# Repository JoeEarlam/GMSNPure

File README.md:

# GMSNPure
An attempt to collate all GMSN's open source designs since the site went offline.

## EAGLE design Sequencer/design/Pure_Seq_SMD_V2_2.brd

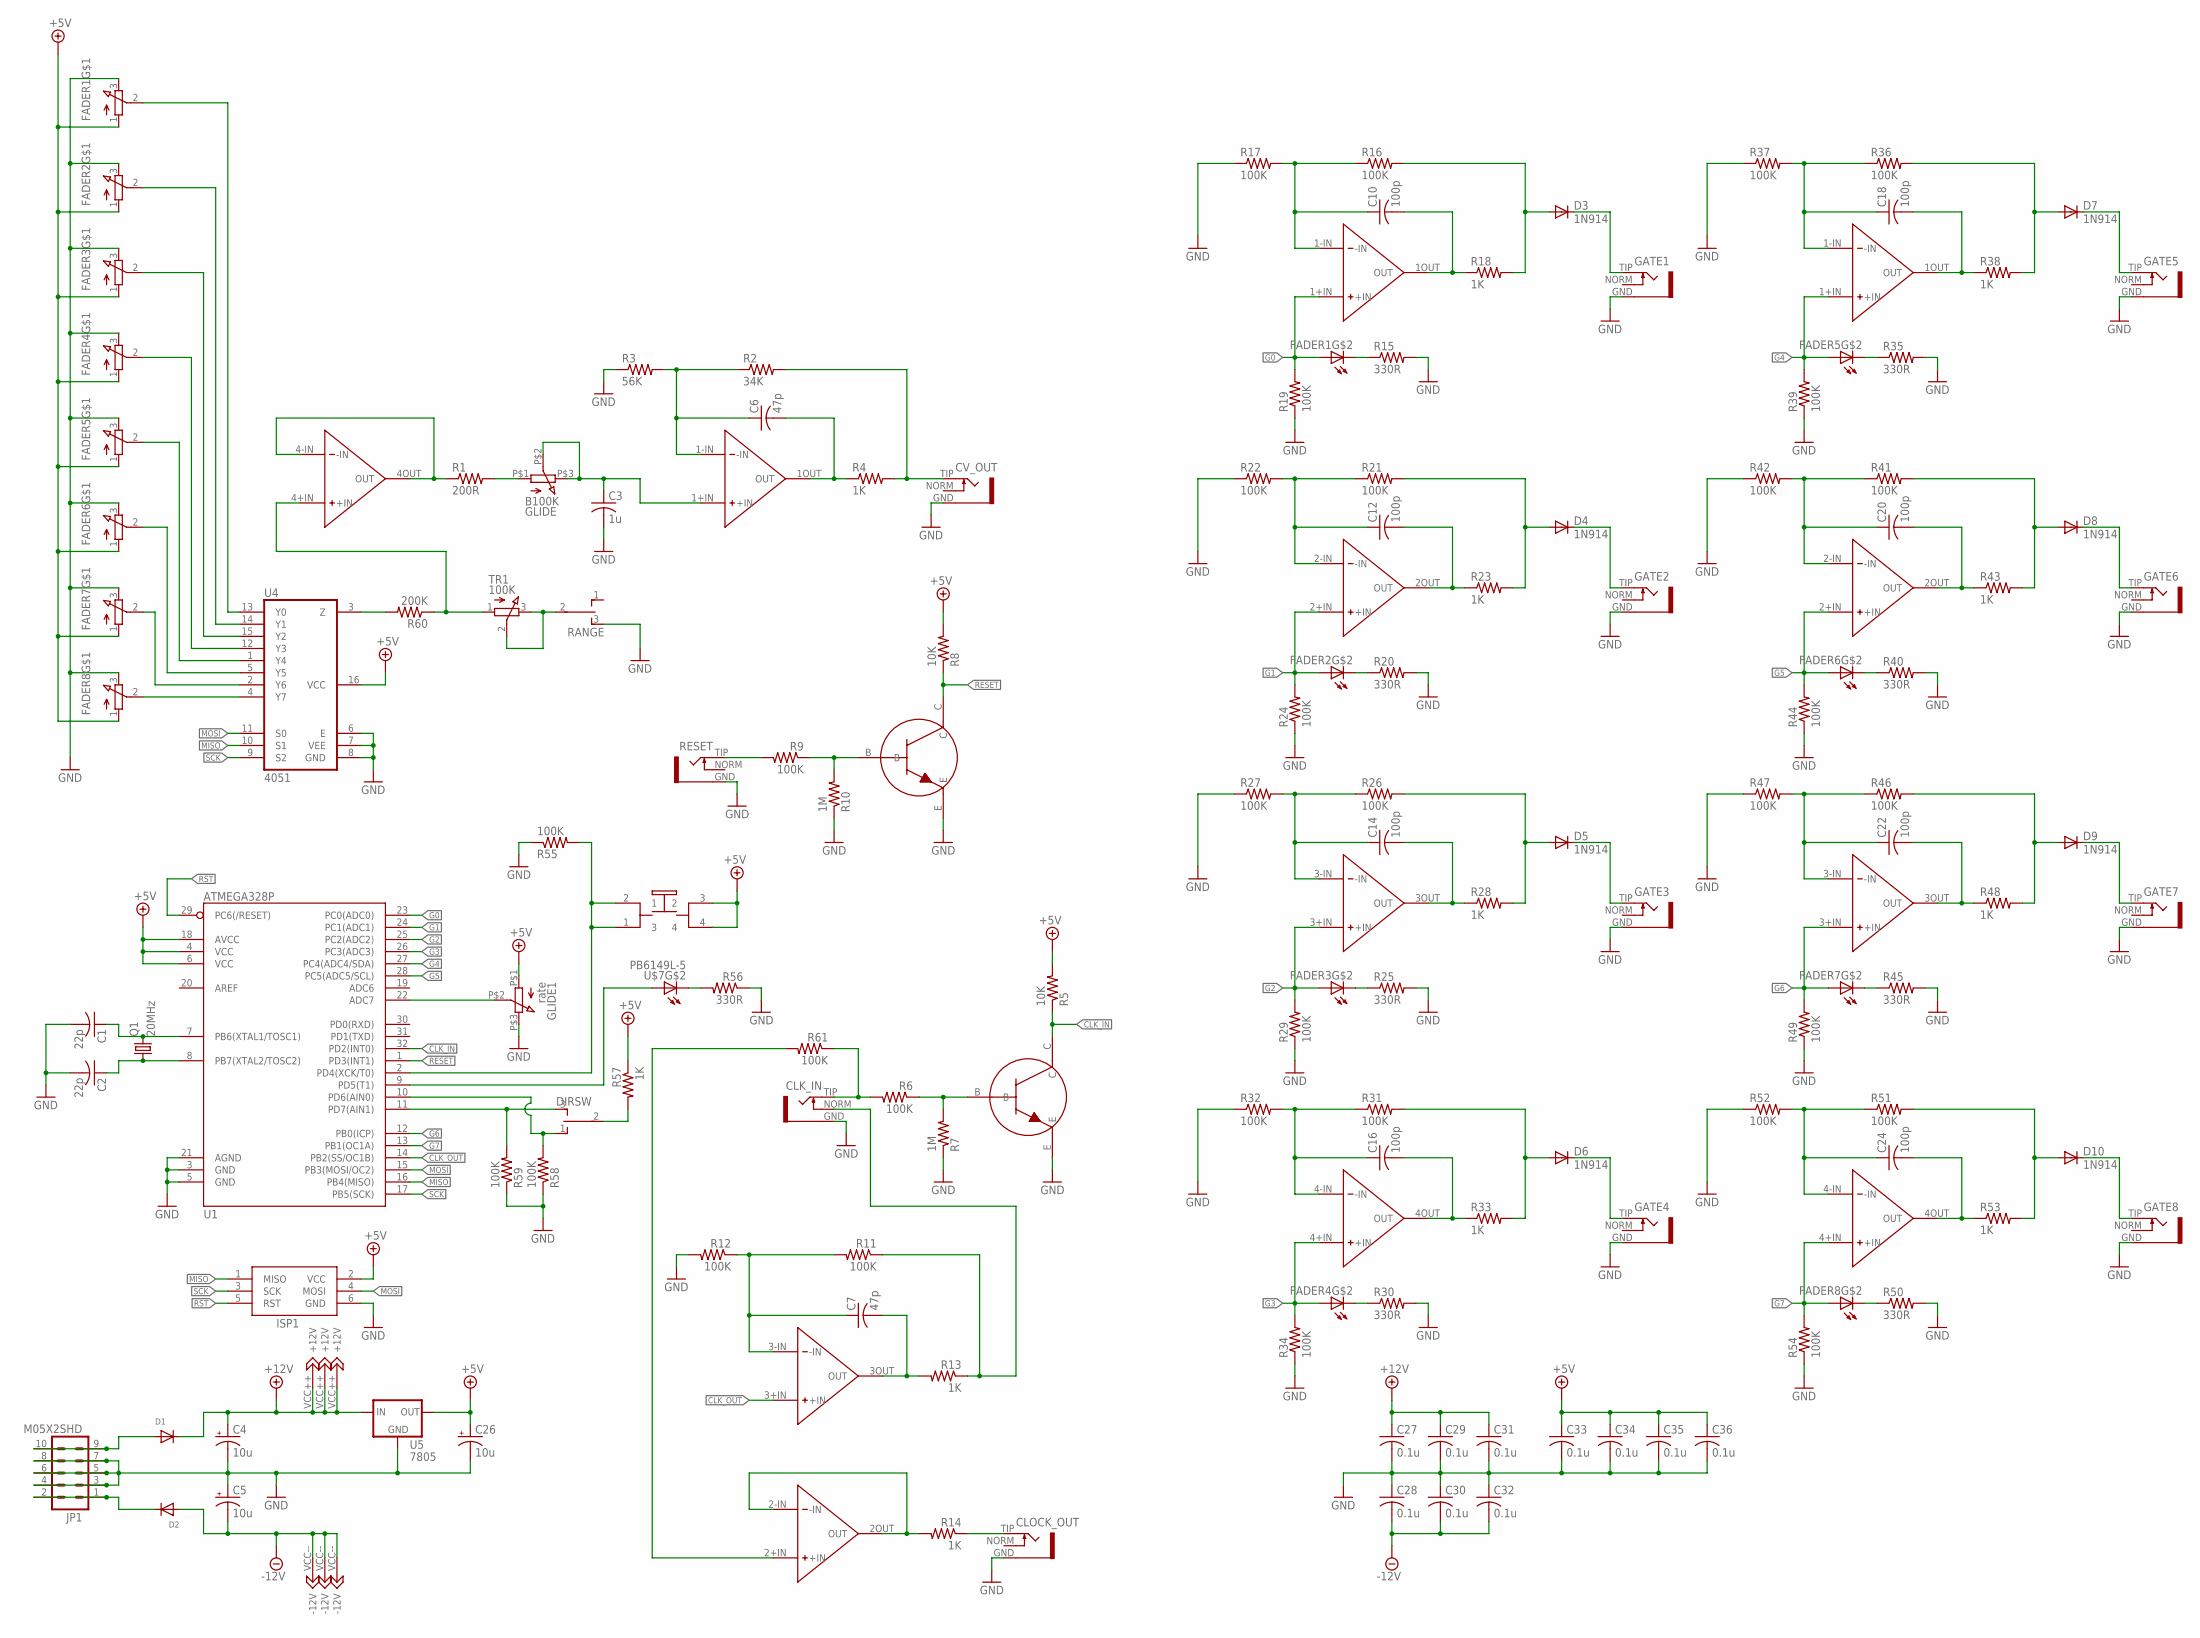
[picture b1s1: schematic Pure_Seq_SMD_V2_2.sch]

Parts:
C1, C2: 22p; C0805K
C3: 1u; C0805K
C4, C5, C26: 10u; 153CLV-0505
C6, C7: 47p; C0805K
C10, C12, C14, C16, C18, C20, C22, C24: 100p; C0805K
C27, C28, C29, C30, C31, C32, C33, C34, C35, C36: 0.1u; C0805K
CLK_IN: S_JACK
CLOCK_OUT: S_JACK
CV_OUT: S_JACK
D1, D2: DIODESMA; SMADIODE
D3, D4, D5, D6, D7, D8, D9, D10: 1N914; SOD-323
DIRSW: TOGGLE_ON_OFF_ON
FADER1, FADER2, FADER3, FADER4, FADER5, FADER6, FADER7, FADER8: LED_FADER
GATE1, GATE2, GATE3, GATE4, GATE5, GATE6, GATE7, GATE8: S_JACK
GLIDE: B100K; Q-POT
GLIDE1: rate; Q-POT
ISP1: AVRISP-6; AVRISP
JP1: M05X2SHD; 2X5-SHROUDED
Q1: 20MHz; HC49UP
R1: 200R; R0805
R2: 34K; R0805
R3: 56K; R0805
R4, R13, R14, R18, R23, R28, R33, R38, R43, R48, R53, R57: 1K; R0805
R5, R8: 10K; R0805
R6, R9, R11, R12, R16, R17, R19, R21, R22, R24, R26, R27, R29, R31, R32, R34, R36, R37, R39, R41, R42, R44, R46, R47, R49, R51, R52, R54, R55, R58, R59, R61: 100K; R0805
R7, R10: 1M; R0805
R15, R20, R25, R30, R35, R40, R45, R50, R56: 330R; R0805
R60: 200K; R0805
RANGE: TOGGLE_ON_OFF_ON
RESET: S_JACK
T1, T2: 2N3904; TRANSISTOR_SINGLE_N-TYPE
TR1: 100K; TRIMMER_TH3
U1: ATMEGA328P; TQFP32-08
U2, U3, U6: QUAD_OPAMP
U4: 4051; N2222_ARRAY
U5: 7805; V-REG
U$7: PB6149L-5; PB6149L

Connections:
+5V: C26.+, C33.1, C34.1, C35.1, C36.1, FADER1.1, FADER2.1, FADER3.1, FADER4.1, FADER5.1, FADER6.1, FADER7.1, FADER8.1, GLIDE1.P$1 (1), ISP1.2 (VCC), R5.2, R8.2, R57.1, U1.4 (VCC), U1.6 (VCC), U1.18 (AVCC), U4.16 (VCC), U5.3 (OUT), U$7.3 (2), U$7.4
+12V: C4.+, C27.1, C29.1, C31.1, D1.C, U2.VCC++ (+12V), U3.VCC++ (+12V), U5.1 (IN), U6.VCC++ (+12V)
-12V: C5.-, C28.2, C30.2, C32.2, D2.A, U2.VCC-- (-12V), U3.VCC-- (-12V), U6.VCC-- (-12V)
CLK_IN: R5.1, T1.C, U1.32 (PD2(INT0))
CLK_OUT: U1.14 (PB2(SS/OC1B)), U6.3+IN (+IN)
G0: FADER1.A, R19.2, U1.23 (PC0(ADC0)), U2.1+IN (+IN)
G1: FADER2.A, R24.2, U1.24 (PC1(ADC1)), U2.2+IN (+IN)
G2: FADER3.A, R29.2, U1.25 (PC2(ADC2)), U2.3+IN (+IN)
G3: FADER4.A, R34.2, U1.26 (PC3(ADC3)), U2.4+IN (+IN)
G4: FADER5.A, R39.2, U1.27 (PC4(ADC4/SDA)), U3.1+IN (+IN)
G5: FADER6.A, R44.2, U1.28 (PC5(ADC5/SCL)), U3.2+IN (+IN)
G6: FADER7.A, R49.2, U1.12 (PB0(ICP)), U3.3+IN (+IN)
G7: FADER8.A, R54.2, U1.13 (PB1(OC1A)), U3.4+IN (+IN)
GND: C1.2, C2.2, C3.2, C4.-, C5.+, C26.-, C27.2, C28.1, C29.2, C30.1, C31.2, C32.1, C33.2, C34.2, C35.2, C36.2, CLK_IN.GND, CLOCK_OUT.GND, CV_OUT.GND, FADER1.3, FADER2.3, FADER3.3, FADER4.3, FADER5.3, FADER6.3, FADER7.3, FADER8.3, GATE1.GND, GATE2.GND, GATE3.GND, GATE4.GND, GATE5.GND, GATE6.GND, GATE7.GND, GATE8.GND, GLIDE1.P$3 (3), ISP1.6 (GND), JP1.3, JP1.4, JP1.5, JP1.6, JP1.7, JP1.8, R3.1, R7.1, R10.1, R12.2, R15.2, R17.1, R19.1, R20.2, R22.1, R24.1, R25.2, R27.1, R29.1, R30.2, R32.1, R34.1, R35.2, R37.1, R39.1, R40.2, R42.1, R44.1, R45.2, R47.1, R49.1, R50.2, R52.1, R54.1, R55.1, R56.1, R58.1, R59.1, RANGE.3 (S), RESET.GND, T1.E, T2.E, U1.3 (GND), U1.5 (GND), U1.21 (AGND), U4.6 (E), U4.7 (VEE), U4.8 (GND), U5.4 (GND)
MISO: ISP1.1 (MISO), U1.16 (PB4(MISO)), U4.10 (S1)
MOSI: ISP1.4 (MOSI), U1.15 (PB3(MOSI/OC2)), U4.11 (S0)
unnamed: C1.1, Q1.2, U1.7 (PB6(XTAL1/TOSC1))
unnamed: C2.1, Q1.1, U1.8 (PB7(XTAL2/TOSC2))
unnamed: R60.1, TR1.1, U6.4+IN (+IN)
unnamed: R1.1, U6.4-IN (-IN), U6.4OUT (OUT)
unnamed: GLIDE.P$1 (1), R1.2
unnamed: FADER8.2, U4.4 (Y7)
unnamed: FADER7.2, U4.2 (Y6)
unnamed: FADER6.2, U4.5 (Y5)
unnamed: D1.A, JP1.9, JP1.10
unnamed: D2.C, JP1.1, JP1.2
unnamed: FADER5.2, U4.1 (Y4)
unnamed: FADER4.2, U4.12 (Y3)
unnamed: FADER3.2, U4.15 (Y2)
unnamed: FADER2.2, U4.14 (Y1)
unnamed: FADER1.2, U4.13 (Y0)
unnamed: C3.1, GLIDE.P$2 (2), GLIDE.P$3 (3), U6.1+IN (+IN)
unnamed: R6.1, R7.2, T1.B
unnamed: R61.2, U6.2+IN (+IN)
unnamed: C6.1, R2.1, R3.2, U6.1-IN (-IN)
unnamed: C6.2, R4.1, U6.1OUT (OUT)
unnamed: CV_OUT.TIP, R2.2, R4.2
unnamed: R9.1, R10.2, T2.B
unnamed: R9.2, RESET.TIP
unnamed: C7.1, R11.2, R12.1, U6.3-IN (-IN)
unnamed: C7.2, R13.2, U6.3OUT (OUT)
unnamed: CLK_IN.TIP, R6.2, R61.1
unnamed: R14.2, U6.2-IN (-IN), U6.2OUT (OUT)
unnamed: CLOCK_OUT.TIP, R14.1
unnamed: CLK_IN.NORM, R11.1, R13.1
unnamed: GLIDE1.P$2 (2), U1.22 (ADC7)
unnamed: FADER1.K (C), R15.1
unnamed: C10.1, R16.1, R17.2, U2.1-IN (-IN)
unnamed: C10.2, R18.1, U2.1OUT (OUT)
unnamed: D3.2 (A), R16.2, R18.2
unnamed: FADER3.K (C), R25.1
unnamed: FADER2.K (C), R20.1
unnamed: C12.1, R21.1, R22.2, U2.2-IN (-IN)
unnamed: C12.2, R23.1, U2.2OUT (OUT)
unnamed: D4.2 (A), R21.2, R23.2
unnamed: C14.1, R26.1, R27.2, U2.3-IN (-IN)
unnamed: C14.2, R28.1, U2.3OUT (OUT)
unnamed: D5.2 (A), R26.2, R28.2
unnamed: FADER4.K (C), R30.1
unnamed: C16.1, R31.1, R32.2, U2.4-IN (-IN)
unnamed: C16.2, R33.1, U2.4OUT (OUT)
unnamed: D6.2 (A), R31.2, R33.2
unnamed: FADER5.K (C), R35.1
unnamed: C18.1, R36.1, R37.2, U3.1-IN (-IN)
unnamed: C18.2, R38.1, U3.1OUT (OUT)
unnamed: D7.2 (A), R36.2, R38.2
unnamed: FADER6.K (C), R40.1
unnamed: C20.1, R41.1, R42.2, U3.2-IN (-IN)
unnamed: C20.2, R43.1, U3.2OUT (OUT)
unnamed: D8.2 (A), R41.2, R43.2
unnamed: FADER7.K (C), R45.1
unnamed: C22.1, R46.1, R47.2, U3.3-IN (-IN)
unnamed: C22.2, R48.1, U3.3OUT (OUT)
unnamed: D9.2 (A), R46.2, R48.2
unnamed: FADER8.K (C), R50.1
unnamed: C24.1, R51.1, R52.2, U3.4-IN (-IN)
unnamed: C24.2, R53.1, U3.4OUT (OUT)
unnamed: D10.2 (A), R51.2, R53.2
unnamed: R55.2, U1.2 (PD4(XCK/T0)), U$7.1 (3), U$7.2 (1)
unnamed: U1.9 (PD5(T1)), U$7.A
unnamed: R56.2, U$7.K (C)
unnamed: DIRSW.2, R57.2
unnamed: DIRSW.1 (O), R58.2, U1.10 (PD6(AIN0))
unnamed: DIRSW.3 (S), R59.2, U1.11 (PD7(AIN1))
unnamed: R60.2, U4.3 (Z)
unnamed: RANGE.2, TR1.2, TR1.3
unnamed: D6.1 (C), GATE4.TIP
unnamed: D5.1 (C), GATE3.TIP
unnamed: D4.1 (C), GATE2.TIP
unnamed: D3.1 (C), GATE1.TIP
unnamed: D10.1 (C), GATE8.TIP
unnamed: D9.1 (C), GATE7.TIP
unnamed: D8.1 (C), GATE6.TIP
unnamed: D7.1 (C), GATE5.TIP
RESET: R8.1, T2.C, U1.1 (PD3(INT1))
RST: ISP1.5 (RST), U1.29 (PC6(/RESET))
SCK: ISP1.3 (SCK), U1.17 (PB5(SCK)), U4.9 (S2)

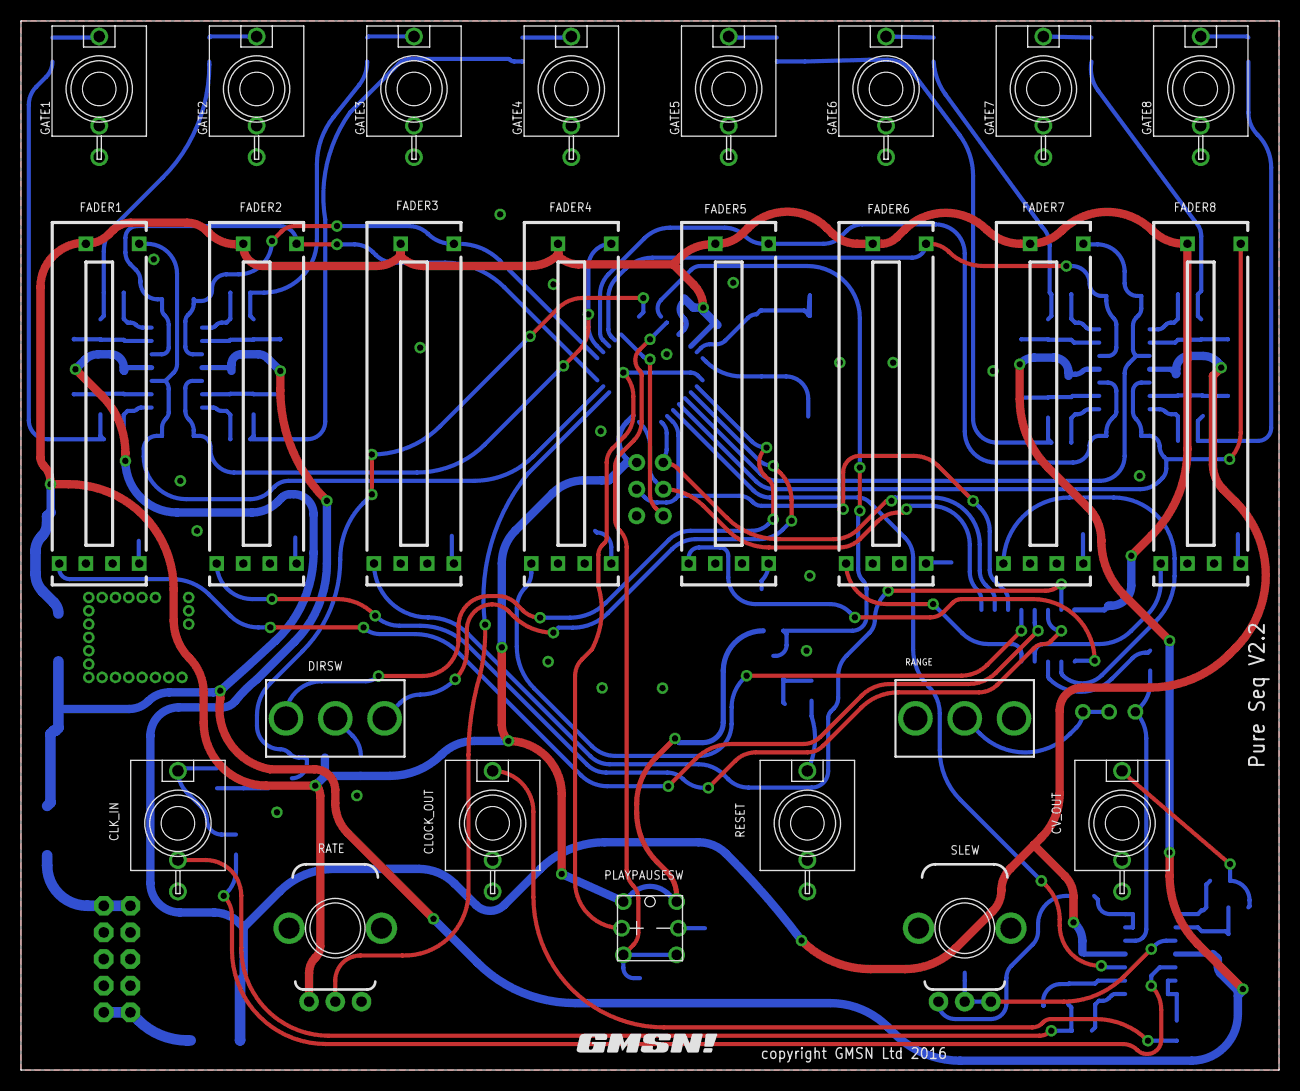
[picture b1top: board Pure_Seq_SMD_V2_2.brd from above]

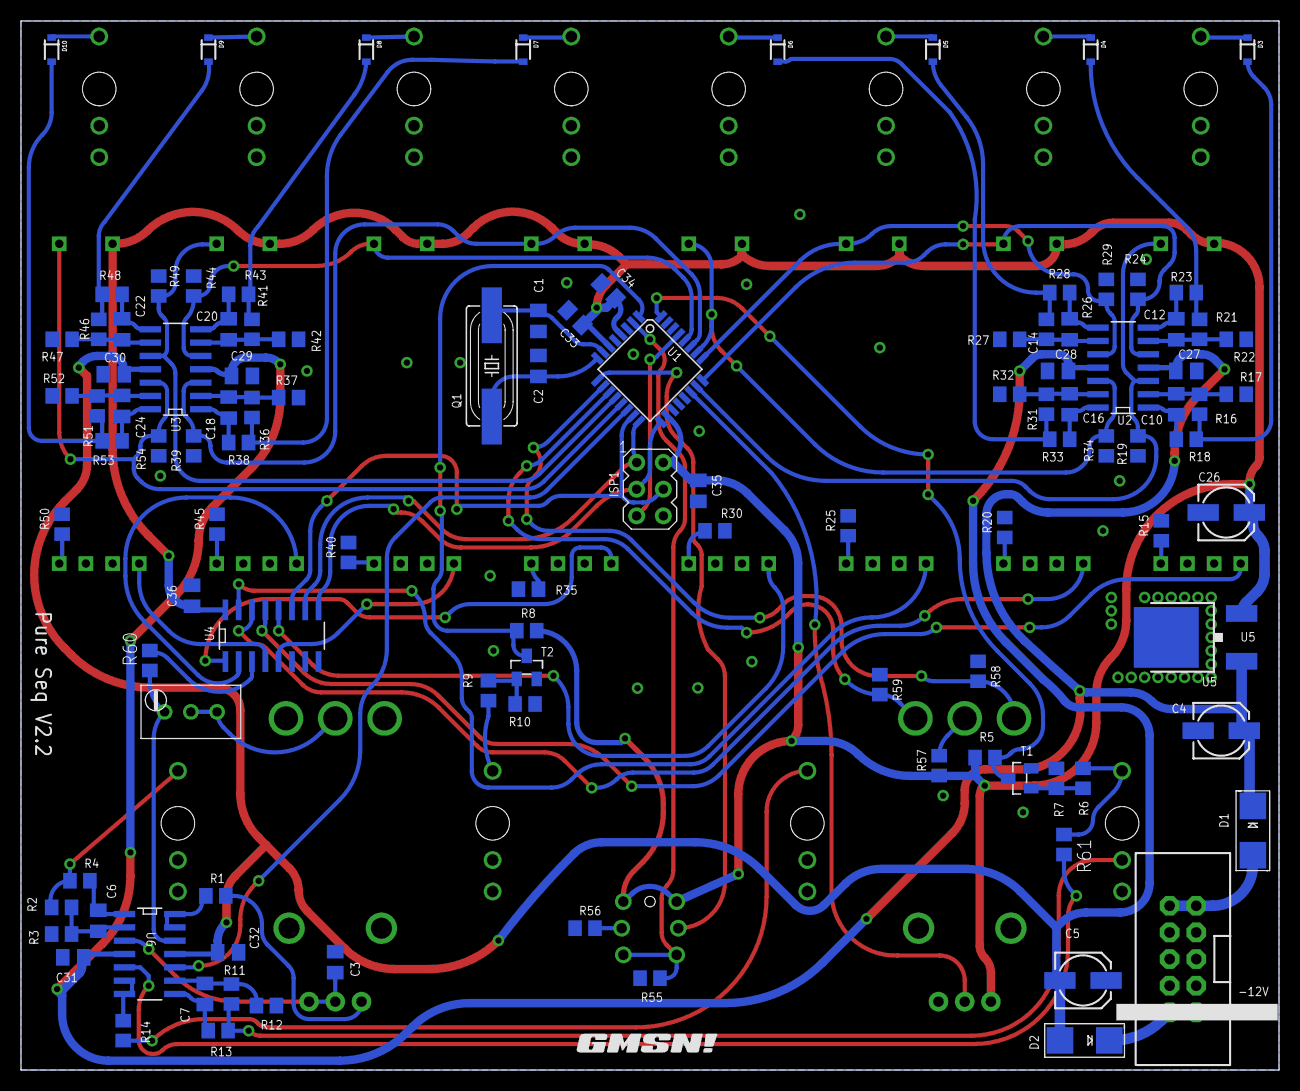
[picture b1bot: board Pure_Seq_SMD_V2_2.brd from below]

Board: 2 copper layers, 119.9 x 100.0 mm, 136 parts (110 on the bottom side), 97 nets.

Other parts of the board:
U$1, U$2: GMSN!_LOGO

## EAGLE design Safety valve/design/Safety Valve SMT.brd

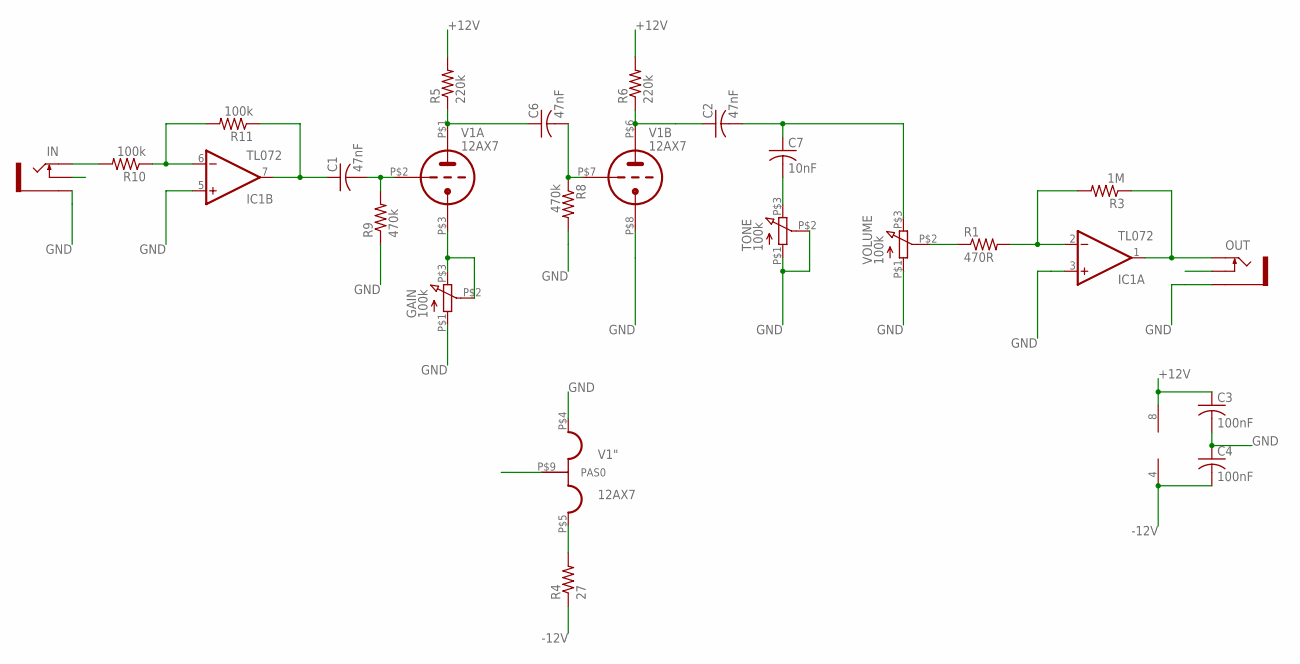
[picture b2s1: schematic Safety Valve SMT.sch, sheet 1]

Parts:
C1, C2, C6: 47nF; C025-024X044
C3, C4: 100nF; C025-024X044
C7: 10nF; C050-024X044
GAIN: 100k; POTENTIOMETER_9MM
IC1: TL072; DIL08
IN: SOCKET_MONO_3.5MMPJ301M-12; PJ301M-12
OUT: SOCKET_MONO_3.5MMPJ301M-12; PJ301M-12
R1: 470R; M0805
R3: 1M; M0805
R4: 27; R0805
R5: 220k; M0805
R6: 220k; R0805
R8, R9: 470k; M0805
R10: 100k; R0805
R11: 100k; M0805
TONE: 100k; POTENTIOMETER_9MM
V1: 12AX7
VOLUME: 100k; POTENTIOMETER_9MM

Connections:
+12V: C3.1, IC1.8 (V+), R5.2, R6.2; also elsewhere on the board
-12V: C4.2, IC1.4 (V-), R4.1; also elsewhere on the board
GND: C3.2, C4.1, GAIN.P$1 (1), IC1.3 (+IN), IC1.5 (+IN), IN.GND (SLEEVE), OUT.GND (SLEEVE), R8.2, R9.1, TONE.P$1 (1), TONE.P$2 (2), V1.P$4 (H1), V1.P$8 (TK), VOLUME.P$1 (1); also elsewhere on the board
unnamed: GAIN.P$2 (2), GAIN.P$3 (3), V1.P$3 (TK)
unnamed: IC1.2 (-IN), R1.2, R3.2
unnamed: C2.2, C7.1, VOLUME.P$3 (3)
unnamed: IC1.1 (OUT), OUT.TIP, R3.1
unnamed: C2.1, R6.1, V1.P$6 (TA)
unnamed: C6.1, R5.1, V1.P$1 (TA)
unnamed: C1.2, R9.2, V1.P$2 (TG)
unnamed: C1.1, IC1.7 (OUT), R11.1
unnamed: R4.2, V1.P$5 (H3)
unnamed: C6.2, R8.1, V1.P$7 (TG)
unnamed: IN.TIP, R10.2
unnamed: C7.2, TONE.P$3 (3)
unnamed: IC1.6 (-IN), R10.1, R11.2
unnamed: R1.1, VOLUME.P$2 (2)

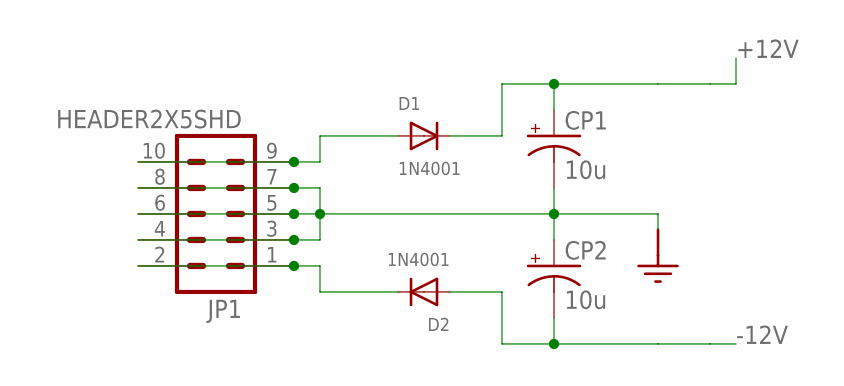
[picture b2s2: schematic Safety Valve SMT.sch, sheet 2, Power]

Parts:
CP1, CP2: 10u; SANYO-OSCON_D
D1, D2: 1N4001; DO-1N4148
JP1: HEADER2X5SHD; 2X5-SHROUDED

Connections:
+12V: CP1.+, D1.C; also elsewhere on the board
-12V: CP2.-, D2.A; also elsewhere on the board
GND: CP1.-, CP2.+, JP1.3, JP1.4, JP1.5, JP1.6, JP1.7, JP1.8; also elsewhere on the board
unnamed: D1.A, JP1.9, JP1.10
unnamed: D2.C, JP1.1, JP1.2

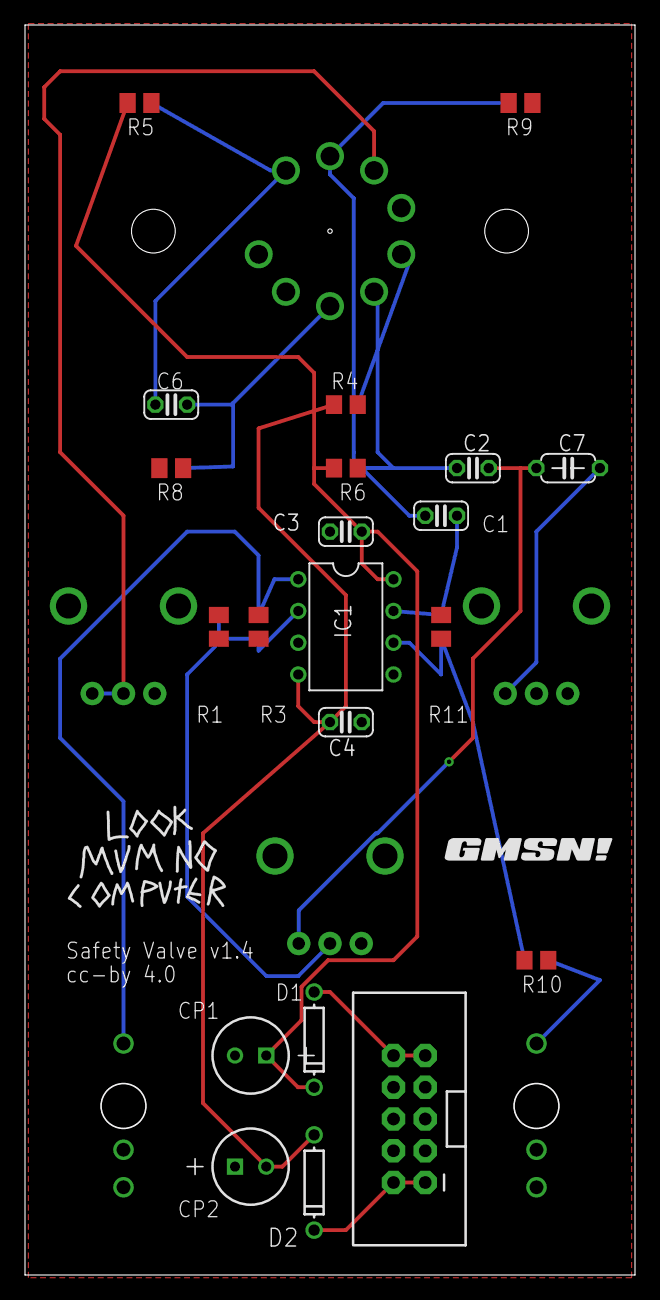
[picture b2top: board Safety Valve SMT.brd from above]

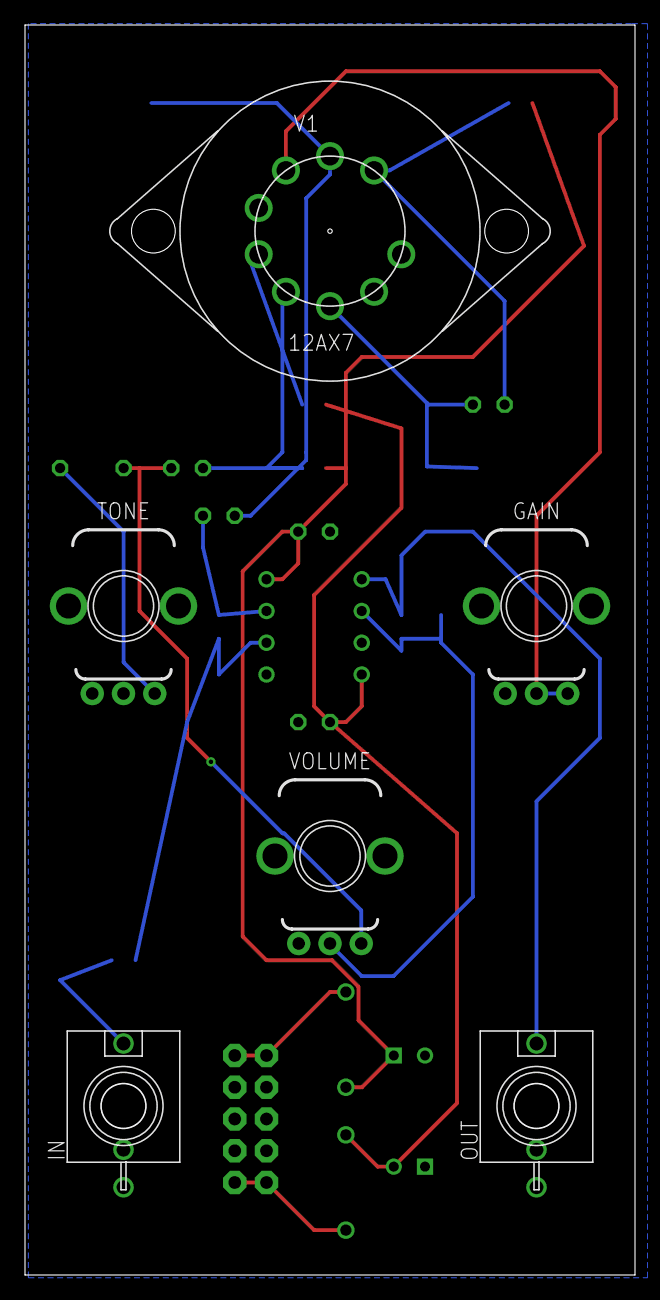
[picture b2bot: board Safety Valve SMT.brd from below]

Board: 2 copper layers, 48.8 x 100.0 mm, 29 parts (6 on the bottom side), 19 nets.

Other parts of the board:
U$1: LMNC_LOGO
U$2: GMSN!_LOGO

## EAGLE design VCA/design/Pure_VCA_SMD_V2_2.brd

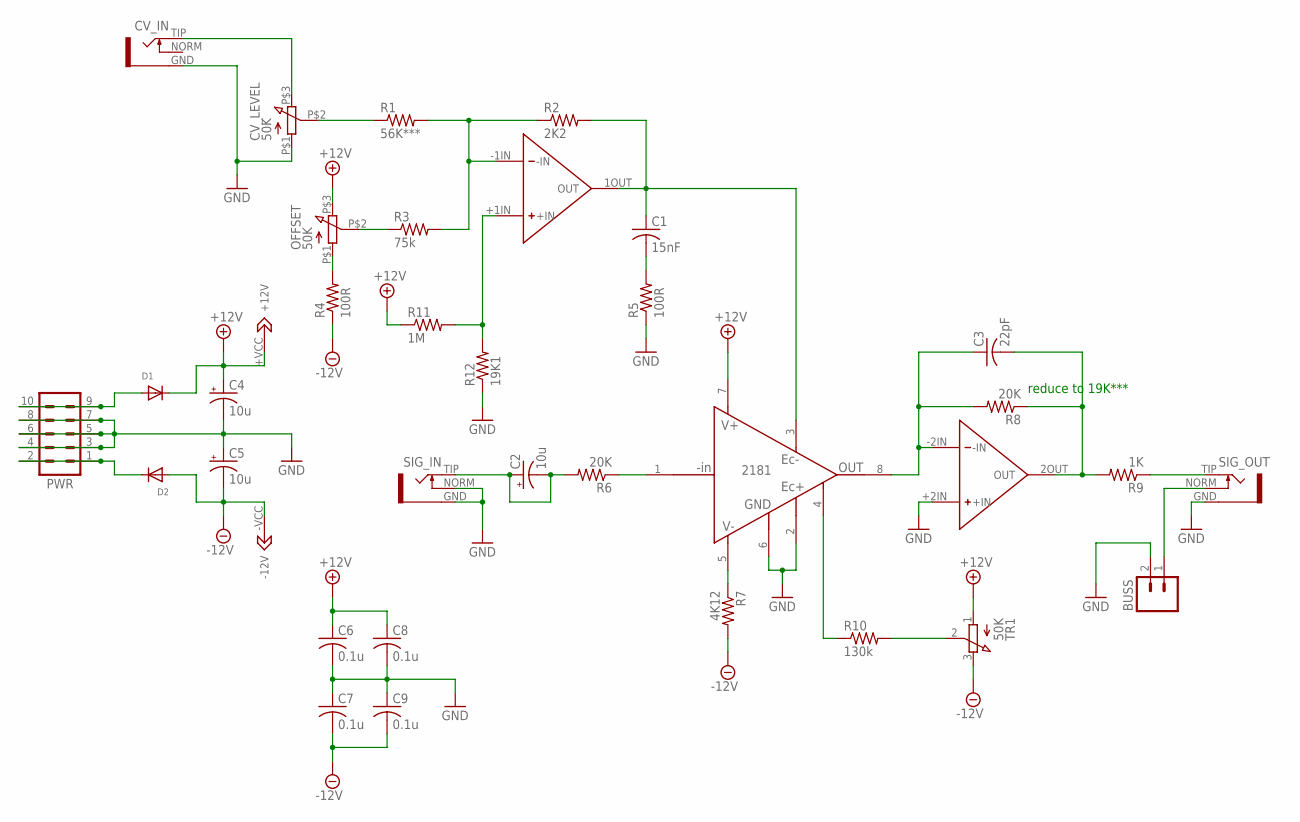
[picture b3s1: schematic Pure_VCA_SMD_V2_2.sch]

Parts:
BUSS: M02PTH; 1X02
C1: 15nF; C0805K
C2, C4, C5: 10u; 153CLV-0505
C3: 22pF; C0805K
C6, C7, C8, C9: 0.1u; C0805K
CV_IN: S_JACK
CV_LEVEL: 50K; Q-POT
D1, D2: DIODESMA; SMADIODE
OFFSET: 50K; Q-POT
PWR: M05X2SHD; 2X5-SHROUDED
R1: 56K***; R0805
R2: 2K2; R0805
R3: 75k; R0805
R4, R5: 100R; R0805
R6, R8: 20K; R0805
R7: 4K12; R0805
R9: 1K; R0805
R10: 130k; R0805
R11: 1M; R0805
R12: 19K1; R0805
SIG_IN: S_JACK
SIG_OUT: S_JACK
TR1: 50K; TRIM_3269W
U1: DUAL_OPAMP
U2: THAT_2181_SMD; SOIC--8

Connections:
+12V: C4.+, C6.1, C8.1, D1.C, OFFSET.P$3 (3), R11.1, TR1.1, U1.+VCC (+12V), U2.7 (V+)
-12V: C5.-, C7.2, C9.2, D2.A, R4.1, R7.2, TR1.3, U1.-VCC (-12V)
GND: BUSS.2, C4.-, C5.+, C6.2, C7.1, C8.2, C9.1, CV_IN.GND, CV_LEVEL.P$1 (1), PWR.3, PWR.4, PWR.5, PWR.6, PWR.7, PWR.8, R5.1, R12.1, SIG_IN.GND, SIG_IN.NORM, SIG_OUT.GND, U1.+2IN (+IN), U2.2 (EC+), U2.6 (GND)
unnamed: CV_IN.TIP, CV_LEVEL.P$3 (3)
unnamed: R1.2, R2.1, R3.2, U1.-1IN (-IN)
unnamed: CV_LEVEL.P$2 (2), R1.1
unnamed: OFFSET.P$1 (1), R4.2
unnamed: C1.1, R2.2, U1.1OUT (OUT), U2.3 (EC-)
unnamed: OFFSET.P$2 (2), R3.1
unnamed: C1.2, R5.2
unnamed: R9.1, SIG_OUT.TIP
unnamed: R6.1, U2.1 (-IN)
unnamed: C2.+, C2.-, R6.2, SIG_IN.TIP
unnamed: BUSS.1, SIG_OUT.NORM
unnamed: R7.1, U2.5 (V-)
unnamed: R11.2, R12.2, U1.+1IN (+IN)
unnamed: C3.1, R8.2, U1.-2IN (-IN), U2.8 (OUT)
unnamed: C3.2, R8.1, R9.2, U1.2OUT (OUT)
unnamed: R10.1, U2.4 (SYM)
unnamed: R10.2, TR1.2
unnamed: D1.A, PWR.9, PWR.10
unnamed: D2.C, PWR.1, PWR.2

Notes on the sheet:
reduce to 19K***

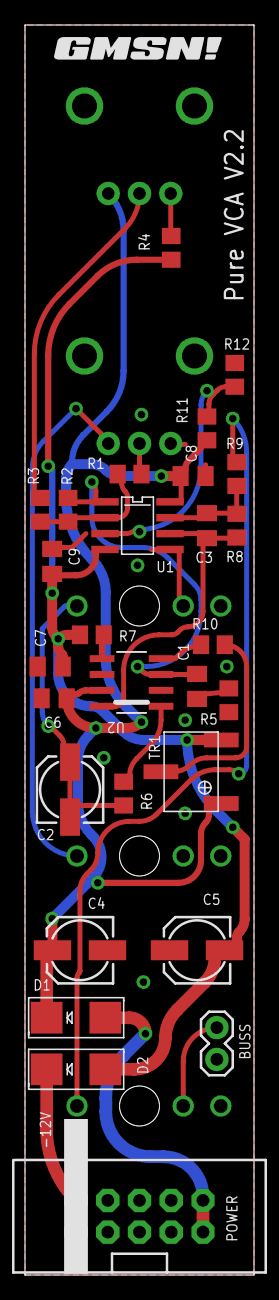
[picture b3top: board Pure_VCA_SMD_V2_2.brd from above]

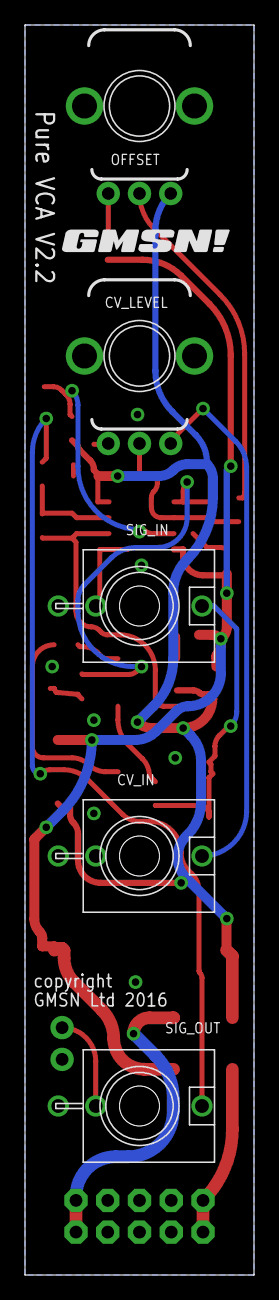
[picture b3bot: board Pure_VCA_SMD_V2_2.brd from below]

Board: 2 copper layers, 18.3 x 100.0 mm, 35 parts (6 on the bottom side), 22 nets.

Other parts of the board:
U$1, U$2: GMSN!_LOGO

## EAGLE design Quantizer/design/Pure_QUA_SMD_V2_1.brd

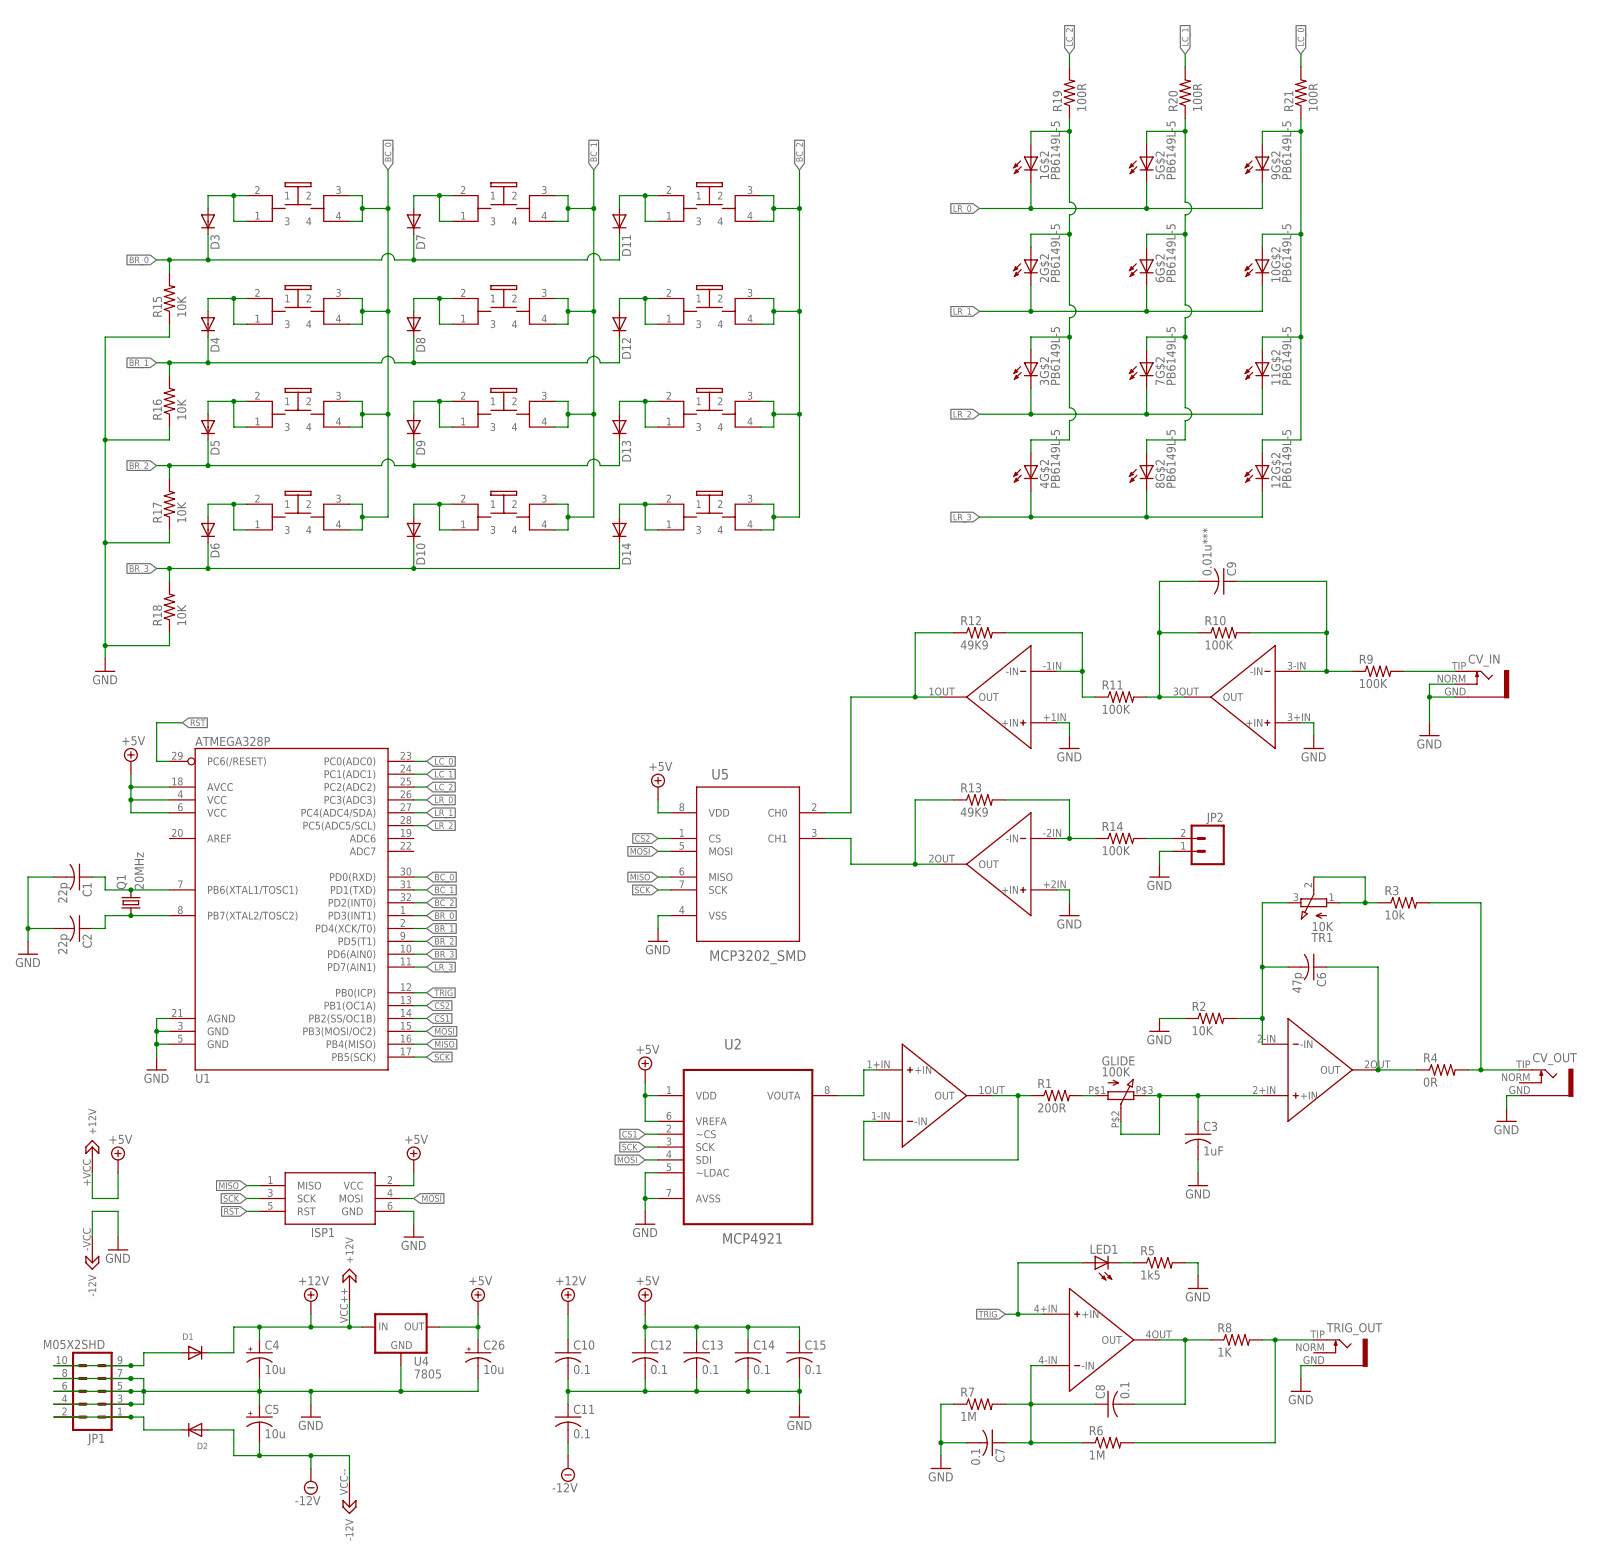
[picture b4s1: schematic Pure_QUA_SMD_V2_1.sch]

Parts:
1, 2, 3, 4, 5, 6, 7, 8, 9, 10, 11, 12: PB6149L-5; PB6149L
C1, C2: 22p; C0805K
C3: 1uF; C0805K
C4, C5, C26: 10u; 153CLV-0505
C6: 47p; C0805K
C7, C8, C10, C11, C12, C13, C14, C15: 0.1; C0805K
C9: 0.01u***; C0805K
CV_IN: S_JACK
CV_OUT: S_JACK
D1, D2: DIODESMA; SMADIODE
D3, D4, D5, D6, D7, D8, D9, D10, D11, D12, D13, D14: DIODESOD; SOD-323
GLIDE: 100K; Q-POT
ISP1: AVRISP-6; AVRISP
JP1: M05X2SHD; 2X5-SHROUDED
JP2: M02PTH; 1X02
LED1: LED5MM
Q1: 20MHz; HC49UP
R1: 200R; R0805
R2, R15, R16, R17, R18: 10K; R0805
R3: 10k; R0805
R4: 0R; R0805
R5: 1k5; R0805
R6, R7: 1M; R0805
R8: 1K; R0805
R9, R10, R11, R14: 100K; R0805
R12, R13: 49K9; R0805
R19, R20, R21: 100R; R0805
TR1: 10K; TRIM_3269W
TRIG_OUT: S_JACK
U1: ATMEGA328P; TQFP32-08
U2: MCP4921; SOIC8
U3: QUAD_OPAMP
U4: 7805; V-REG
U5: MCP3202_SMD; SOIC--8
U6: DUAL_OPAMP

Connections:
+5V: C12.1, C13.1, C14.1, C15.1, C26.+, ISP1.2 (VCC), U1.4 (VCC), U1.6 (VCC), U1.18 (AVCC), U2.1 (VDD), U2.6 (VREFA), U4.3 (OUT), U5.8 (VDD), U6.+VCC (+12V)
+12V: C4.+, C10.1, D1.C, U3.VCC++ (+12V), U4.1 (IN)
-12V: C5.-, C11.2, D2.A, U3.VCC-- (-12V)
BC_0: 1.3 (2), 1.4, 2.3 (2), 2.4, 3.3 (2), 3.4, 4.3 (2), 4.4, U1.30 (PD0(RXD))
BC_1: 5.3 (2), 5.4, 6.3 (2), 6.4, 7.3 (2), 7.4, 8.3 (2), 8.4, U1.31 (PD1(TXD))
BC_2: 9.3 (2), 9.4, 10.3 (2), 10.4, 11.3 (2), 11.4, 12.3 (2), 12.4, U1.32 (PD2(INT0))
BR_0: D3.1 (C), D7.1 (C), D11.1 (C), R15.2, U1.1 (PD3(INT1))
BR_1: D4.1 (C), D8.1 (C), D12.1 (C), R16.2, U1.2 (PD4(XCK/T0))
BR_2: D5.1 (C), D9.1 (C), D13.1 (C), R17.2, U1.9 (PD5(T1))
BR_3: D6.1 (C), D10.1 (C), D14.1 (C), R18.2, U1.10 (PD6(AIN0))
CS1: U1.14 (PB2(SS/OC1B)), U2.2 (~CS)
CS2: U1.13 (PB1(OC1A)), U5.1 (CS)
GND: C1.2, C2.2, C3.2, C4.-, C5.+, C7.2, C10.2, C11.1, C12.2, C13.2, C14.2, C15.2, C26.-, CV_IN.GND, CV_IN.NORM, CV_OUT.GND, ISP1.6 (GND), JP1.3, JP1.4, JP1.5, JP1.6, JP1.7, JP1.8, JP2.1, R2.1, R5.2, R7.1, R15.1, R16.1, R17.1, R18.1, TRIG_OUT.GND, U1.3 (GND), U1.5 (GND), U1.21 (AGND), U2.5 (~LDAC), U2.7 (AVSS), U3.3+IN (+IN), U4.4 (GND), U5.4 (VSS), U6.+1IN (+IN), U6.+2IN (+IN), U6.-VCC (-12V)
LC_0: R21.2, U1.23 (PC0(ADC0))
LC_1: R20.2, U1.24 (PC1(ADC1))
LC_2: R19.2, U1.25 (PC2(ADC2))
LR_0: 1.K (C), 5.K (C), 9.K (C), U1.26 (PC3(ADC3))
LR_1: 2.K (C), 6.K (C), 10.K (C), U1.27 (PC4(ADC4/SDA))
LR_2: 3.K (C), 7.K (C), 11.K (C), U1.28 (PC5(ADC5/SCL))
LR_3: 4.K (C), 8.K (C), 12.K (C), U1.11 (PD7(AIN1))
MISO: ISP1.1 (MISO), U1.16 (PB4(MISO)), U5.6 (MISO)
MOSI: ISP1.4 (MOSI), U1.15 (PB3(MOSI/OC2)), U2.4 (SDI), U5.5 (MOSI)
unnamed: C1.1, Q1.2, U1.7 (PB6(XTAL1/TOSC1))
unnamed: C2.1, Q1.1, U1.8 (PB7(XTAL2/TOSC2))
unnamed: U2.8 (VOUTA), U3.1+IN (+IN)
unnamed: R1.1, U3.1-IN (-IN), U3.1OUT (OUT)
unnamed: GLIDE.P$1 (1), R1.2
unnamed: C3.1, GLIDE.P$2 (2), GLIDE.P$3 (3), U3.2+IN (+IN)
unnamed: R3.1, TR1.1, TR1.2
unnamed: CV_OUT.TIP, R3.2, R4.2
unnamed: D1.A, JP1.9, JP1.10
unnamed: D2.C, JP1.1, JP1.2
unnamed: C6.1, R4.1, U3.2OUT (OUT)
unnamed: C6.2, R2.2, TR1.3, U3.2-IN (-IN)
unnamed: C7.1, C8.1, R6.1, R7.2, U3.4-IN (-IN)
unnamed: LED1.K (C), R5.1
unnamed: R6.2, R8.2, TRIG_OUT.TIP
unnamed: C8.2, R8.1, U3.4OUT (OUT)
unnamed: C9.1, R9.1, R10.2, U3.3-IN (-IN)
unnamed: CV_IN.TIP, R9.2
unnamed: R12.1, U5.2 (CH0), U6.1OUT (OUT)
unnamed: R11.1, R12.2, U6.-1IN (-IN)
unnamed: C9.2, R10.1, R11.2, U3.3OUT (OUT)
unnamed: 1.1 (3), 1.2 (1), D3.2 (A)
unnamed: R13.1, U5.3 (CH1), U6.2OUT (OUT)
unnamed: R13.2, R14.1, U6.-2IN (-IN)
unnamed: JP2.2, R14.2
unnamed: 2.1 (3), 2.2 (1), D4.2 (A)
unnamed: 3.1 (3), 3.2 (1), D5.2 (A)
unnamed: 4.1 (3), 4.2 (1), D6.2 (A)
unnamed: 5.1 (3), 5.2 (1), D7.2 (A)
unnamed: 6.1 (3), 6.2 (1), D8.2 (A)
unnamed: 7.1 (3), 7.2 (1), D9.2 (A)
unnamed: 8.1 (3), 8.2 (1), D10.2 (A)
unnamed: 9.1 (3), 9.2 (1), D11.2 (A)
unnamed: 10.1 (3), 10.2 (1), D12.2 (A)
unnamed: 11.1 (3), 11.2 (1), D13.2 (A)
unnamed: 12.1 (3), 12.2 (1), D14.2 (A)
unnamed: 1.A, 2.A, 3.A, 4.A, R19.1
unnamed: 5.A, 6.A, 7.A, 8.A, R20.1
unnamed: 9.A, 10.A, 11.A, 12.A, R21.1
RST: ISP1.5 (RST), U1.29 (PC6(/RESET))
SCK: ISP1.3 (SCK), U1.17 (PB5(SCK)), U2.3 (SCK), U5.7 (SCK)
TRIG: LED1.A, U1.12 (PB0(ICP)), U3.4+IN (+IN)

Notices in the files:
Quantizer/code/pureQuantiser.ino:
cc-by 4.0
ADSR/design/Pure ADSR.brd:
copyright GMSN Ltd 2016
parts and their libraries:
SparkFun-Connectors: Licensing: CC v3.0 Share-Alike You are welcome to use this library for commercial purposes.
